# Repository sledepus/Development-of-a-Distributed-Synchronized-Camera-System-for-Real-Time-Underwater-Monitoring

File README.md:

# Development of a Distributed Synchronized Camera System for Real-Time Underwater Monitoring
<div style="text-align: center;">
    
</div>

This is the Git repository of the bachelor thesis "Development of a Distributed Synchronized Camera System for Real-Time Underwater Monitoring", carried out at the University of Agder by students from the Mechatronics and Electronics engineering programs.

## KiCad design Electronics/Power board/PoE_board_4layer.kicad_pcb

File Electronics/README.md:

# KiCAD projects for power board and sensor board
BOM for boards are found in their respective folder. PCBs were ordered from JLCPCB, with the power board requiring a specific stackup which can be found in "Specifications for JLCPCB.txt". The sensor board could be ordered with the normal stackup.

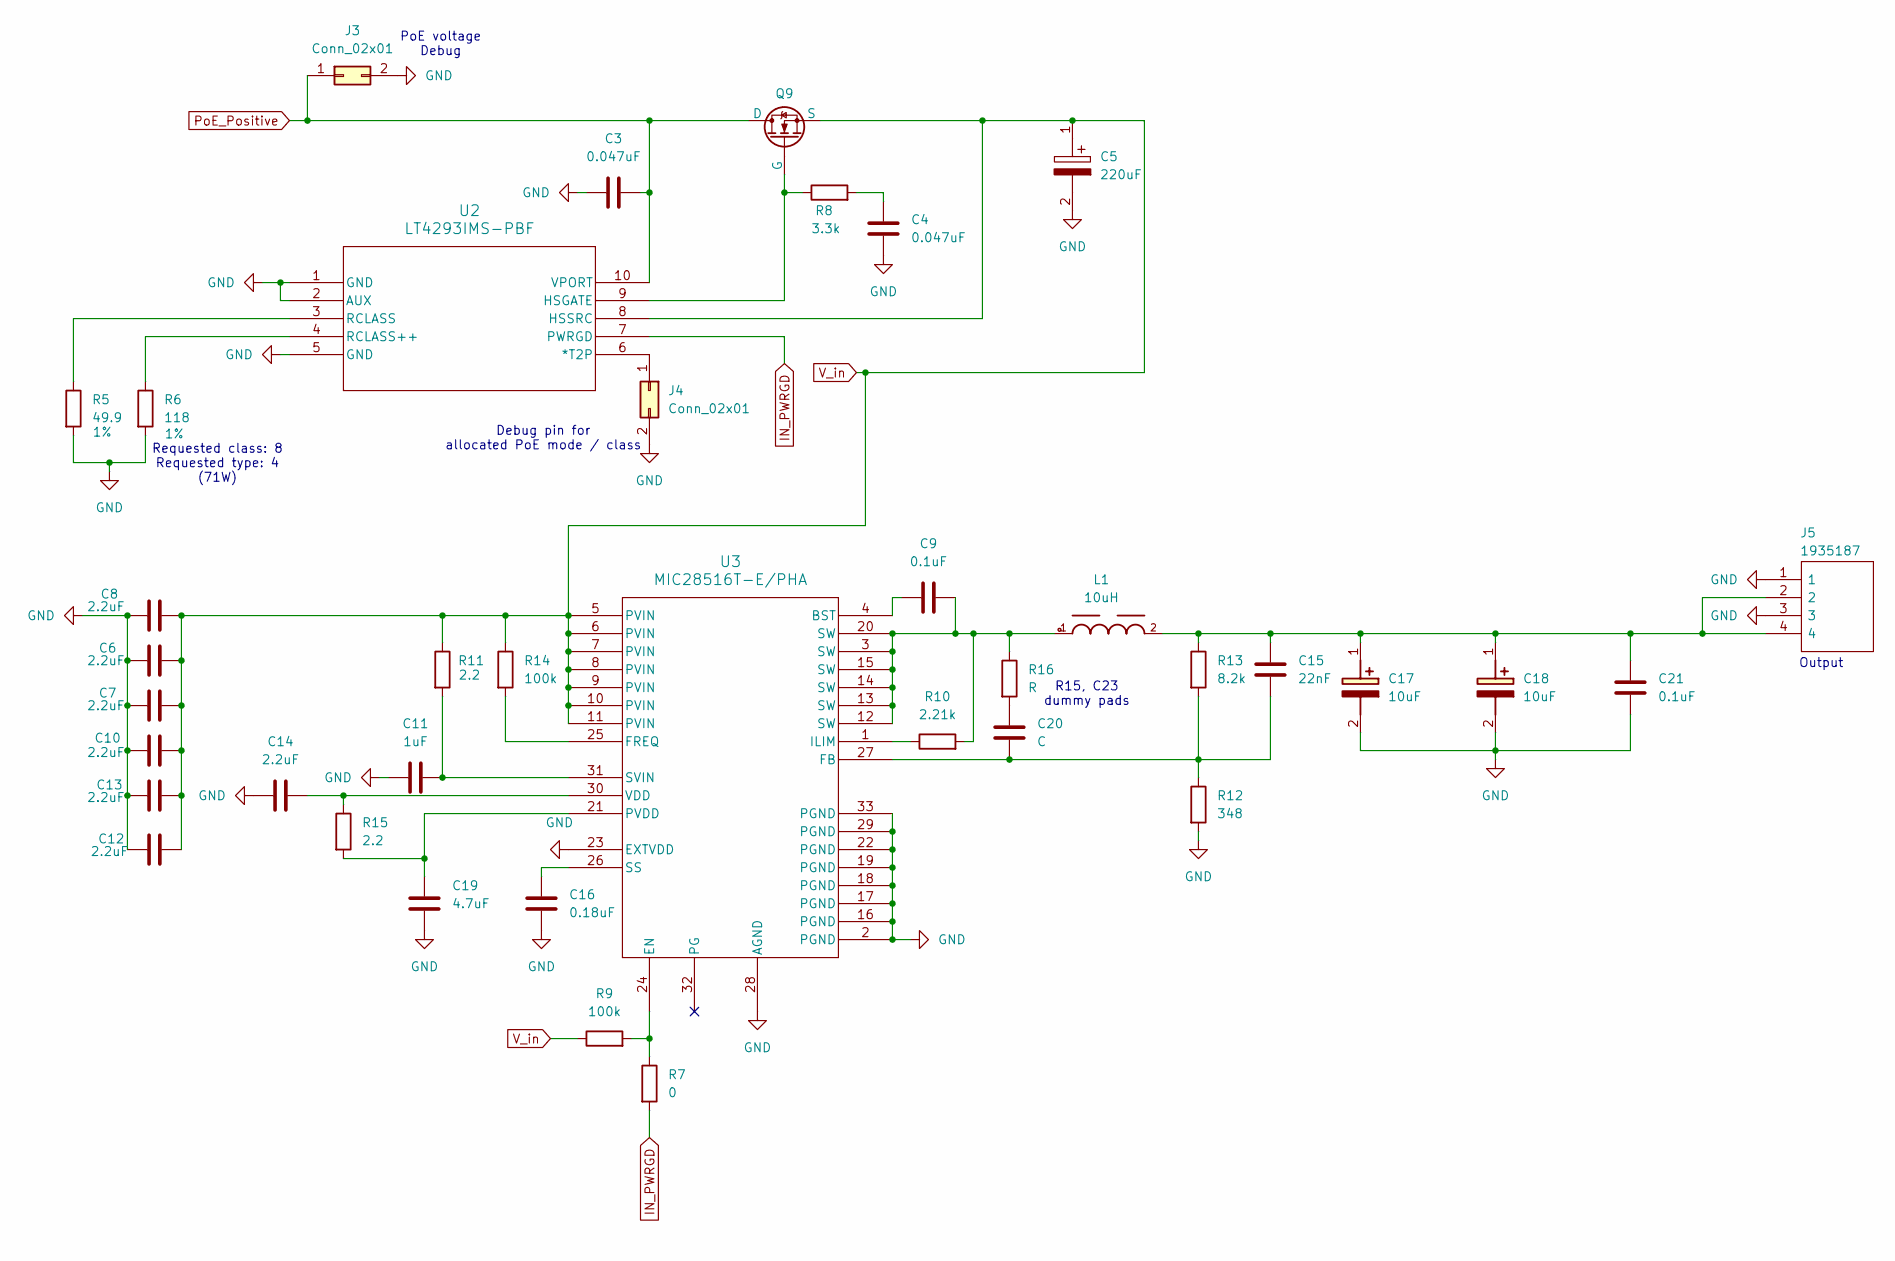
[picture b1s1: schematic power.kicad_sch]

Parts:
C3, C4: 0.047uF; C_1206_3216Metric_Pad1.33x1.80mm_HandSolder
C5: 220uF; CAPPRD500W65D1250H2700; Mouser Part Number 667-EEU-FS2A221B
C6, C7, C8, C10, C12, C13, C14: 2.2uF; C_1206_3216Metric
C9: 0.1uF; C_0603_1608Metric_Pad1.08x0.95mm_HandSolder
C11: 1uF; C_0603_1608Metric_Pad1.08x0.95mm_HandSolder
C15: 22nF; C_0603_1608Metric_Pad1.08x0.95mm_HandSolder
C16: 0.18uF; C_0603_1608Metric_Pad1.08x0.95mm_HandSolder
C17, C18: 10uF; 16SVF82M; Mouser Part Number 667-20SVPA10M
C19: 4.7uF; C_1206_3216Metric_Pad1.33x1.80mm_HandSolder
C20: C; C_1206_3216Metric_Pad1.33x1.80mm_HandSolder
C21: 0.1uF; C_1206_3216Metric_Pad1.33x1.80mm_HandSolder
J3, J4: Conn_02x01; PinHeader_2x01_P2.54mm_Vertical
J5: 1935187; Mouser Part Number 651-1935187
L1: 10uH; WE-XHMI_1090
Q9: PSMN040-100MSE; LFPAK33
R5: 49.9; R_0603_1608Metric_Pad0.98x0.95mm_HandSolder; Tolerance 1%
R6: 118; R_0603_1608Metric_Pad0.98x0.95mm_HandSolder; Tolerance 1%
R7: 0; R_1206_3216Metric_Pad1.30x1.75mm_HandSolder
R8: 3.3k; R_0603_1608Metric_Pad0.98x0.95mm_HandSolder
R9, R14: 100k; R_0603_1608Metric_Pad0.98x0.95mm_HandSolder
R10: 2.21k; R_0603_1608Metric_Pad0.98x0.95mm_HandSolder
R11, R15: 2.2; R_0603_1608Metric_Pad0.98x0.95mm_HandSolder
R12: 348; R_0603_1608Metric_Pad0.98x0.95mm_HandSolder
R13: 8.2k; R_0603_1608Metric_Pad0.98x0.95mm_HandSolder
R16: R; R_1206_3216Metric_Pad1.30x1.75mm_HandSolder
U2: LT4293IMS-PBF; 05-08-1661_ADI
U3: MIC28516T-E/PHA; VQFN32_6X6_3EP_PHA_MCH

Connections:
GND: C3.1, C4.2, C5.2, C6.1, C7.1, C8.1, C10.1, C11.2, C12.1, C13.1, C14.1, C16.2, C17.2 (-), C18.2 (-), C19.2, C21.2, J3.2, J4.2, J5.1, J5.3, R5.2, R6.2, R12.2, U2.1 (GND), U2.2 (AUX), U2.5 (GND), U3.2 (PGND), U3.16 (PGND), U3.17 (PGND), U3.18 (PGND), U3.19 (PGND), U3.22 (PGND), U3.23 (EXTVDD), U3.28 (AGND), U3.29 (PGND), U3.33 (PGND); also elsewhere on the board
IN_PWRGD: R7.2, U2.7 (PWRGD); also elsewhere on the board
unnamed: C4.1, R8.2
unnamed: C9.2, L1.1, R10.2, R16.1, U3.3 (SW), U3.12 (SW), U3.13 (SW), U3.14 (SW), U3.15 (SW), U3.20 (SW)
unnamed: C15.1, C17.1 (+), C18.1 (+), C21.1, J5.2, J5.4, L1.2, R13.1
unnamed: C20.1, R16.2
unnamed: J4.1, U2.6 (*T2P)
unnamed: Q9.4 (G), R8.1, U2.9 (HSGATE)
unnamed: R5.1, U2.3 (RCLASS)
unnamed: R6.1, U2.4 (RCLASS++)
unnamed: C9.1, U3.4 (BST)
unnamed: R7.1, R9.2, U3.24 (EN)
unnamed: C15.2, C20.2, R12.1, R13.2, U3.27 (FB)
unnamed: R14.2, U3.25 (FREQ)
unnamed: R10.1, U3.1 (ILIM)
unnamed: C19.1, R15.2, U3.21 (PVDD)
unnamed: C16.1, U3.26 (SS)
unnamed: C11.1, R11.2, U3.31 (SVIN)
unnamed: C14.2, R15.1, U3.30 (VDD)
PoE_Positive: C3.2, J3.1, Q9.5 (D), U2.10 (VPORT); also elsewhere on the board
V_in: C5.1, C6.2, C7.2, C8.2, C10.2, C12.2, C13.2, Q9.1 (S), Q9.2 (S), Q9.3 (S), R9.1, R11.1, R14.1, U2.8 (HSSRC), U3.5 (PVIN), U3.6 (PVIN), U3.7 (PVIN), U3.8 (PVIN), U3.9 (PVIN), U3.10 (PVIN), U3.11 (PVIN)

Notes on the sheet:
Requested class: 8 Requested type: 4 (71W)
PoE voltage Debug
Output
Debug pin for allocated PoE mode / class
R15, C23 dummy pads

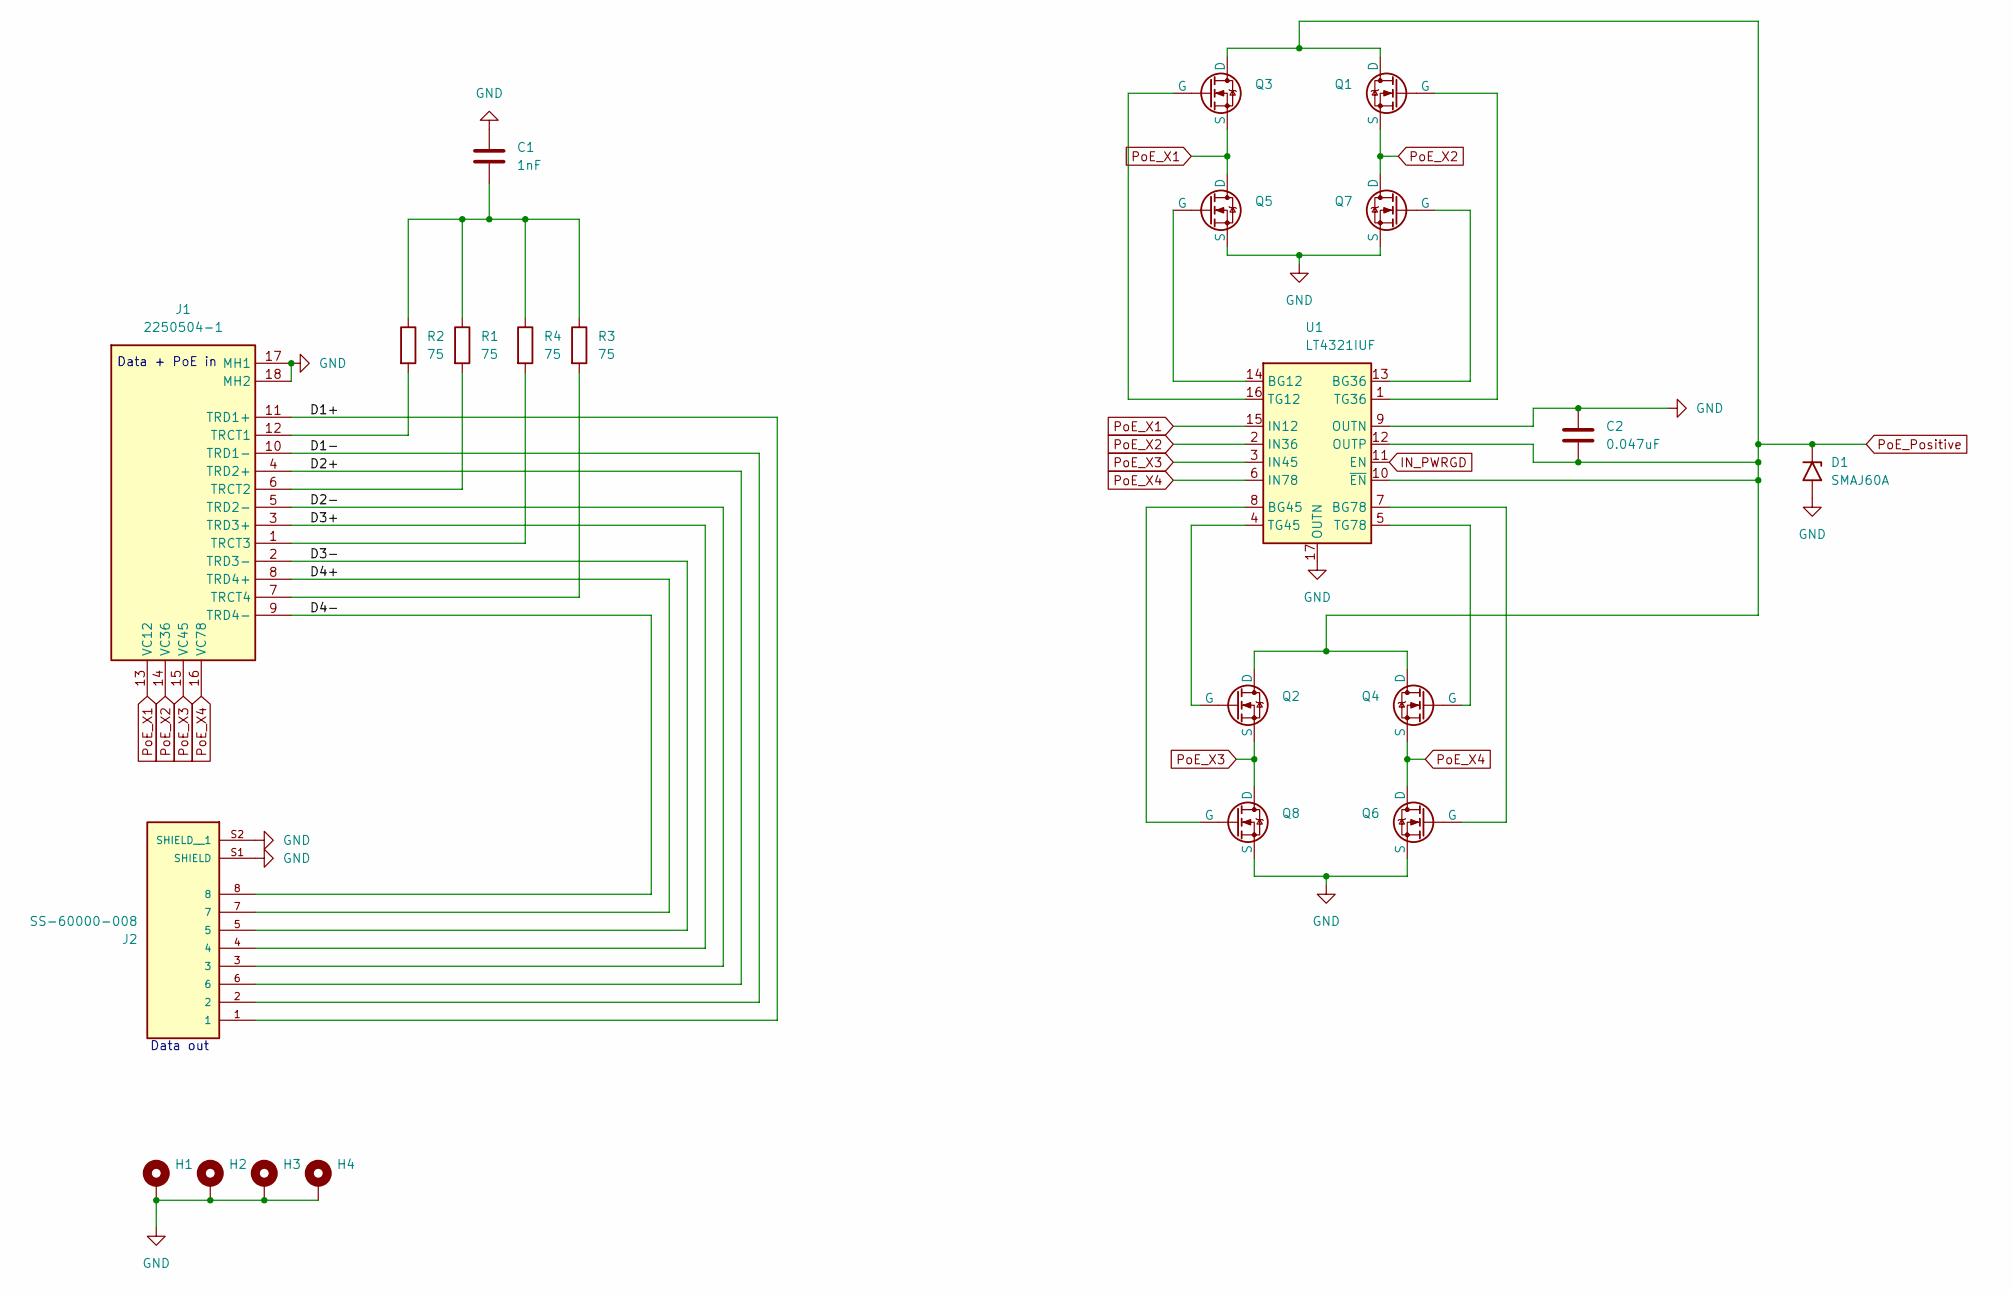
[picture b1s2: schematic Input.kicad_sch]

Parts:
C1: 1nF; C_1808_4520Metric_Pad1.72x2.30mm_HandSolder
C2: 0.047uF; C_1206_3216Metric_Pad1.33x1.80mm_HandSolder
D1: SMAJ60A; D_SMA
H1, H2, H3, H4: MountingHole_Pad; MountingHole_3.2mm_M3_Pad
J1: 2250504-1; 22505041; Mouser Part Number 530-2250504-1
J2: SS-60000-008; BEL_SS-60000-008; PARTREV C6
Q1, Q2, Q3, Q4, Q5, Q6, Q7, Q8: PSMN040-100MSE; LFPAK33
R1, R2, R3, R4: 75; R_1206_3216Metric_Pad1.30x1.75mm_HandSolder
U1: LT4321IUF; QFN-16-1EP_4x4mm_P0.65mm_EP2.15x2.15mm

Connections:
/Input/D1+: J1.11 (TRD1+), J2.1
/Input/D1-: J1.10 (TRD1-), J2.2
/Input/D2+: J1.4 (TRD2+), J2.6
/Input/D2-: J1.5 (TRD2-), J2.3
/Input/D3+: J1.3 (TRD3+), J2.4
/Input/D3-: J1.2 (TRD3-), J2.5
/Input/D4+: J1.8 (TRD4+), J2.7
/Input/D4-: J1.9 (TRD4-), J2.8
GND: C1.1, C2.1, D1.2 (A2), H1.1, H2.1, H3.1, H4.1, J1.17 (MH1), J1.18 (MH2), J2.S1 (SHIELD), J2.S2 (SHIELD__1), Q5.1 (S), Q5.2 (S), Q5.3 (S), Q6.1 (S), Q6.2 (S), Q6.3 (S), Q7.1 (S), Q7.2 (S), Q7.3 (S), Q8.1 (S), Q8.2 (S), Q8.3 (S), U1.9 (OUTN), U1.17 (OUTN); also elsewhere on the board
IN_PWRGD: U1.11 (EN); also elsewhere on the board
unnamed: C1.2, R1.1, R2.1, R3.1, R4.1
unnamed: J1.12 (TRCT1), R2.2
unnamed: J1.6 (TRCT2), R1.2
unnamed: J1.1 (TRCT3), R4.2
unnamed: J1.7 (TRCT4), R3.2
unnamed: Q1.4 (G), U1.1 (TG36)
unnamed: Q2.4 (G), U1.4 (TG45)
unnamed: Q3.4 (G), U1.16 (TG12)
unnamed: Q4.4 (G), U1.5 (TG78)
unnamed: Q5.4 (G), U1.14 (BG12)
unnamed: Q6.4 (G), U1.7 (BG78)
unnamed: Q7.4 (G), U1.13 (BG36)
unnamed: Q8.4 (G), U1.8 (BG45)
PoE_Positive: C2.2, D1.1 (A1), Q1.5 (D), Q2.5 (D), Q3.5 (D), Q4.5 (D), U1.10 (~EN), U1.12 (OUTP); also elsewhere on the board
PoE_X1: J1.13 (VC12), Q3.1 (S), Q3.2 (S), Q3.3 (S), Q5.5 (D), U1.15 (IN12)
PoE_X2: J1.14 (VC36), Q1.1 (S), Q1.2 (S), Q1.3 (S), Q7.5 (D), U1.2 (IN36)
PoE_X3: J1.15 (VC45), Q2.1 (S), Q2.2 (S), Q2.3 (S), Q8.5 (D), U1.3 (IN45)
PoE_X4: J1.16 (VC78), Q4.1 (S), Q4.2 (S), Q4.3 (S), Q6.5 (D), U1.6 (IN78)

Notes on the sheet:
Data + PoE in
Data out

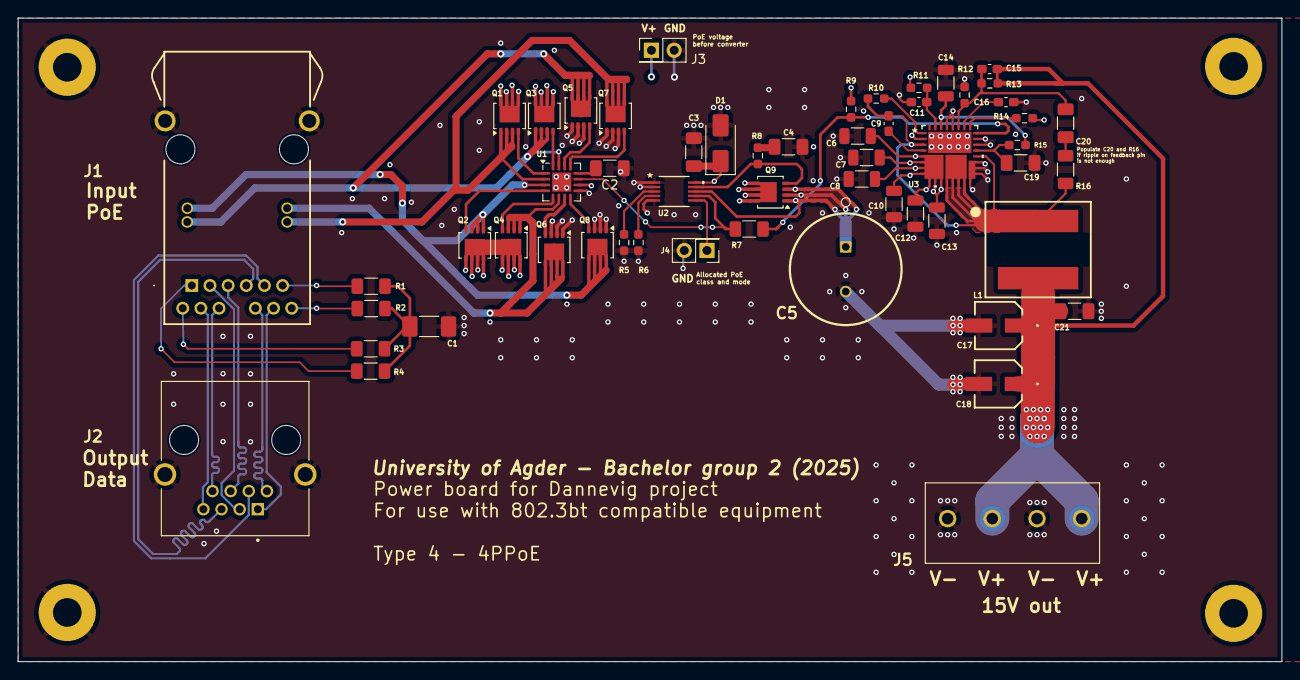
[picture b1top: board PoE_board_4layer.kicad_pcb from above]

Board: 4 copper layers, 141.4 x 72.0 mm, 60 parts (0 on the bottom side), 46 nets.

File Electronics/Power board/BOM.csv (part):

Reference,Value,,Footprint,Qty,DNP,,Cost,Link,,,,,,,,,,,,Total cost:,616.35
C1,1nF,,Capacitor_SMD:C_1808_4520Metric_Pad1.72x2.30mm_HandSolder,1,,,6.33,https://no.mouser.com/ProductDetail/TDK/C4520X7R3D102K130KA?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,,,,,,,,,,,,,
C2,0.047uF,,Capacitor_SMD:C_1206_3216Metric_Pad1.33x1.80mm_HandSolder,1,,,5.06,https://no.mouser.com/ProductDetail/TDK/C3216X7R2A474K160AA?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,,,,,,,,,,,,,
C3,0.047uF,,Capacitor_SMD:C_1206_3216Metric_Pad1.33x1.80mm_HandSolder,1,,,5.06,https://no.mouser.com/ProductDetail/TDK/C3216X7R2A474K160AA?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,,,,,,,,,,,,,
C4,0.047uF,,Capacitor_SMD:C_1206_3216Metric_Pad1.33x1.80mm_HandSolder,1,,,5.06,https://no.mouser.com/ProductDetail/TDK/C3216X7R2A474K160AA?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,,,,,,,,,,,,,
C5,220uF,,local symbols:CAPPRD500W65D1250H2700,1,,,18.63,https://no.mouser.com/ProductDetail/Panasonic/EEU-FS2A221B?q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,,,,,,,,,,,,,
C6,2.2uF,,Capacitor_SMD:C_1206_3216Metric,1,,,5.06,https://no.mouser.com/ProductDetail/Samsung-Electro-Mechanic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,,,,,,,,,,,,,
C7,2.2uF,,Capacitor_SMD:C_1206_3216Metric,1,,,5.06,https://no.mouser.com/ProductDetail/Samsung-Electro-Mechanic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,,,,,,,,,,,,,
C8,2.2uF,,Capacitor_SMD:C_1206_3216Metric,1,,,5.06,https://no.mouser.com/ProductDetail/Samsung-Electro-Mechanic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,,,,,,,,,,,,,
C9,0.1uF,,Capacitor_SMD:C_0603_1608Metric_Pad1.08x0.95mm_HandSolder,1,,,1.15,https://no.mouser.com/ProductDetail/Samsung-Electro-Mechanic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,,,,,,,,,,,,,
C10,2.2uF,,Capacitor_SMD:C_1206_3216Metric,1,,,5.06,https://no.mouser.com/ProductDetail/Samsung-Electro-Mechanic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,,,,,,,,,,,,,
C11,1uF,,Capacitor_SMD:C_0603_1608Metric_Pad1.08x0.95mm_HandSolder,1,,,3.11,https://no.mouser.com/ProductDetail/TDK/C1608X7R2A105K080AC?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,,,,,,,,,,,,,
C12,2.2uF,,Capacitor_SMD:C_1206_3216Metric,1,,,5.06,https://no.mouser.com/ProductDetail/Samsung-Electro-Mechanic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,,,,,,,,,,,,,
C13,2.2uF,,Capacitor_SMD:C_1206_3216Metric,1,,,5.06,https://no.mouser.com/ProductDetail/Samsung-Electro-Mechanic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,,,,,,,,,,,,,
C14,2.2uF,,Capacitor_SMD:C_1206_3216Metric,1,,,5.06,https://no.mouser.com/ProductDetail/Samsung-Electro-Mechanic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,,,,,,,,,,,,,
C15,22nF,,Capacitor_SMD:C_0603_1608Metric_Pad1.08x0.95mm_HandSolder,1,,,1.15,https://no.mouser.com/ProductDetail/TDK/C1608X7R1H223K080AA?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,,,,,,,,,,,,,
C16,0.18uF,,Capacitor_SMD:C_0603_1608Metric_Pad1.08x0.95mm_HandSolder,1,,,2.07,https://no.mouser.com/ProductDetail/Murata-Electronics/GRM18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,,,,,,,,,,,,,
C17,20SVPA10M,,local symbols:16SVF82M,1,,,10.12,https://no.mouser.com/ProductDetail/Panasonic/20SVPA10M?qs=k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,,,,,,,,,,,,,
C18,20SVPA10M,,local symbols:16SVF82M,1,,,10.12,https://no.mouser.com/ProductDetail/Panasonic/20SVPA10M?qs=k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,,,,,,,,,,,,,
C19,4.7uF,,Capacitor_SMD:C_1206_3216Metric_Pad1.33x1.80mm_HandSolder,1,,,3.34,https://no.mouser.com/ProductDetail/TDK/C3216X7R1E475K160AC?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,,,,,,,,,,,,,
C20,C,,Capacitor_SMD:C_0603_1608Metric_Pad1.08x0.95mm_HandSolder,1,,,DNP,DNP,,,,,,,,,,,,,
C21,0.1uF,,Capacitor_SMD:C_1206_3216Metric_Pad1.33x1.80mm_HandSolder,1,,,2.76,https://no.mouser.com/ProductDetail/TDK/C3216X7R2A104M160AA?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,,,,,,,,,,,,,
D1,SMAJ60A,,Diode_SMD:D_SMA,1,,,3.11,https://no.mouser.com/ProductDetail/Littelfuse/SMAJ60A?qs=JJ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,,,,,,,,,,,,,
J1,2250504-1,,local symbols:22505041,1,,,103.33,https://no.mouser.com/ProductDetail/TRP-Connector-Bel/225050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,,,,,,,,,,,,,
J2,SS-60000-008,,local symbols:BEL_SS-60000-008,1,,,42.71,https://no.mouser.com/ProductDetail/Stewart-Connector-Bel/SS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,,,,,,,,,,,,,
J3,Conn_02x01,,Connector_PinHeader_2.54mm:PinHeader_2x01_P2.54mm_Vertical,1,,,DNP,DNP,,,,,,,,,,,,,
J4,Conn_02x01,,Connector_PinHeader_2.54mm:PinHeader_2x01_P2.54mm_Vertical,1,,,DNP,DNP,,,,,,,,,,,,,
J5,1935187,,local symbols:1935187,1,,,11.16,https://no.mouser.com/ProductDetail/Phoenix-Contact/1935187?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,,,,,,,,,,,,,
L1,10uH,,local symbols:WE-XHMI_1090,1,,,63.77,https://no.mouser.com/ProductDetail/Wurth-Elektronik/7443936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,,,,,,,,,,,,,
Q1,PSMN040-100MSE,,Package_TO_SOT_SMD:LFPAK33,1,,,12.95,https://no.mouser.com/ProductDetail/Nexperia/PSMN040-100MSEX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,,,,,,,,,,,,,
Q2,PSMN040-100MSE,,Package_TO_SOT_SMD:LFPAK33,1,,,12.95,https://no.mouser.com/ProductDetail/Nexperia/PSMN040-100MSEX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,,,,,,,,,,,,,
Q3,PSMN040-100MSE,,Package_TO_SOT_SMD:LFPAK33,1,,,12.95,https://no.mouser.com/ProductDetail/Nexperia/PSMN040-100MSEX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,,,,,,,,,,,,,
Q4,PSMN040-100MSE,,Package_TO_SOT_SMD:LFPAK33,1,,,12.95,https://no.mouser.com/ProductDetail/Nexperia/PSMN040-100MSEX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,,,,,,,,,,,,,
Q5,PSMN040-100MSE,,Package_TO_SOT_SMD:LFPAK33,1,,,12.95,https://no.mouser.com/ProductDetail/Nexperia/PSMN040-100MSEX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,,,,,,,,,,,,,
Q6,PSMN040-100MSE,,Package_TO_SOT_SMD:LFPAK33,1,,,12.95,https://no.mouser.com/ProductDetail/Nexperia/PSMN040-100MSEX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,,,,,,,,,,,,,
Q7,PSMN040-100MSE,,Package_TO_SOT_SMD:LFPAK33,1,,,12.95,https://no.mouser.com/ProductDetail/Nexperia/PSMN040-100MSEX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,,,,,,,,,,,,,
Q8,PSMN040-100MSE,,Package_TO_SOT_SMD:LFPAK33,1,,,12.95,https://no.mouser.com/ProductDetail/Nexperia/PSMN040-100MSEX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,,,,,,,,,,,,,
Q9,PSMN040-100MSE,,Package_TO_SOT_SMD:LFPAK33,1,,,12.95,https://no.mouser.com/ProductDetail/Nexperia/PSMN040-100MSEX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,,,,,,,,,,,,,
R1,75,,Resistor_SMD:R_1206_3216Metric_Pad1.30x1.75mm_HandSolder,1,,,1.15,https://no.mouser.com/ProductDetail/YAGEO/RT1206DRE0775RL?qs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,,,,,,,,,,,,,
R2,75,,Resistor_SMD:R_1206_3216Metric_Pad1.30x1.75mm_HandSolder,1,,,1.15,https://no.mouser.com/ProductDetail/YAGEO/RT1206DRE0775RL?qs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,,,,,,,,,,,,,
R3,75,,Resistor_SMD:R_1206_3216Metric_Pad1.30x1.75mm_HandSolder,1,,,1.15,https://no.mouser.com/ProductDetail/YAGEO/RT1206DRE0775RL?qs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,,,,,,,,,,,,,
R4,75,,Resistor_SMD:R_1206_3216Metric_Pad1.30x1.75mm_HandSolder,1,,,1.15,https://no.mouser.com/ProductDetail/YAGEO/RT1206DRE0775RL?qs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,,,,,,,,,,,,,
R5,49.9,,Resistor_SMD:R_0603_1608Metric_Pad0.98x0.95mm_HandSolder,1,,,1.5,https://no.mouser.com/ProductDetail/Vishay-Dale/RCS060349R9F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,,,,,,,,,,,,,
R6,118,,Resistor_SMD:R_0603_1608Metric_Pad0.98x0.95mm_HandSolder,1,,,1.22,https://no.mouser.com/ProductDetail/KOA-Speer/RK73H1JTTD1180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,,,,,,,,,,,,,
R7,0,,Resistor_SMD:R_1206_3216Metric_Pad1.30x1.75mm_HandSolder,1,,,1.15,https://no.mouser.com/ProductDetail/Vishay-Dale/CRCW12060000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,,,,,,,,,,,,,
R8,3.3k,,Resistor_SMD:R_0603_1608Metric_Pad0.98x0.95mm_HandSolder,1,,,1.15,https://no.mouser.com/ProductDetail/YAGEO/AC0603JR-073K3L?qs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,,,,,,,,,,,,,
R9,100k,,Resistor_SMD:R_0603_1608Metric_Pad0.98x0.95mm_HandSolder,1,,,1.15,https://no.mouser.com/ProductDetail/YAGEO/AT0603FRE07100KL?q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,,,,,,,,,,,,,
R10,2.21k,,Resistor_SMD:R_0603_1608Metric_Pad0.98x0.95mm_HandSolder,1,,,1.15,https://no.mouser.com/ProductDetail/Panasonic/ERJ-3EKF2211V?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,,,,,,,,,,,,,
R11,2.2,,Resistor_SMD:R_0603_1608Metric_Pad0.98x0.95mm_HandSolder,1,,,2.42,https://no.mouser.com/ProductDetail/Vishay-Dale/RCS06032R20F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,,,,,,,,,,,,,
R12,348,,Resistor_SMD:R_0603_1608Metric_Pad0.98x0.95mm_HandSolder,1,,,2.42,https://no.mouser.com/ProductDetail/Panasonic/ERJ-H3EF3480V?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,,,,,,,,,,,,,
R13,8.2k,,Resistor_SMD:R_0603_1608Metric_Pad0.98x0.95mm_HandSolder,1,,,1.61,https://no.mouser.com/ProductDetail/Vishay-Dale/RCS06038K20F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,,,,,,,,,,,,,
R14,100k,,Resistor_SMD:R_0603_1608Metric_Pad0.98x0.95mm_HandSolder,1,,,1.15,https://no.mouser.com/ProductDetail/YAGEO/AT0603FRE07100KL?q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,,,,,,,,,,,,,
R15,2.2,,Resistor_SMD:R_0603_1608Metric_Pad0.98x0.95mm_HandSolder,1,,,2.42,https://no.mouser.com/ProductDetail/Vishay-Dale/RCS06032R20F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,,,,,,,,,,,,,
R16,R,,Resistor_SMD:R_0603_1608Metric_Pad0.98x0.95mm_HandSolder,1,,,DNP,DNP,,,,,,,,,,,,,
U1,LT4321IUF,,Package_DFN_QFN:QFN-16-1EP_4x4mm_P0.65mm_EP2.15x2.15mm,1,,,46.39,https://www.digikey.no/no/products/detail/analog-devices-inc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,,,,,,,,,,,,,
U2,LT4293IMS-PBF,,footprints:05-08-1661_ADI,1,,,58.08,https://no.mouser.com/ProductDetail/Analog-Devices/LT4293IMS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,,,,,,,,,,,,,
U3,MIC28516T-E/PHA,,footprints:VQFN32_6X6_3EP_PHA_MCH,1,,,39.93,https://no.mouser.com/ProductDetail/Microchip-Technology/MIC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,,,,,,,,,,,,,
,,,,,,,,,,,,,,,,,,,,,
,,,,,,,,,,,,,,,,,,,,,
,,,,,,,,,,,,,,,,,,,,,
,,,,,,,,,,,,,,,,,,,,,
,Komponenter til 1 kort,616.35,,,,,,,,,,,,,,,,,,,
,Bestilling av 5 kort (uten stencil),832.44,,,,,,,,,,,,,,,,,,,
,eller,,,,,,,,,,,,,,,,,,,,
,Bestilling av 5 kort (med stencil),1172.45,,,,,,,,,,,,,,,,,,,
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
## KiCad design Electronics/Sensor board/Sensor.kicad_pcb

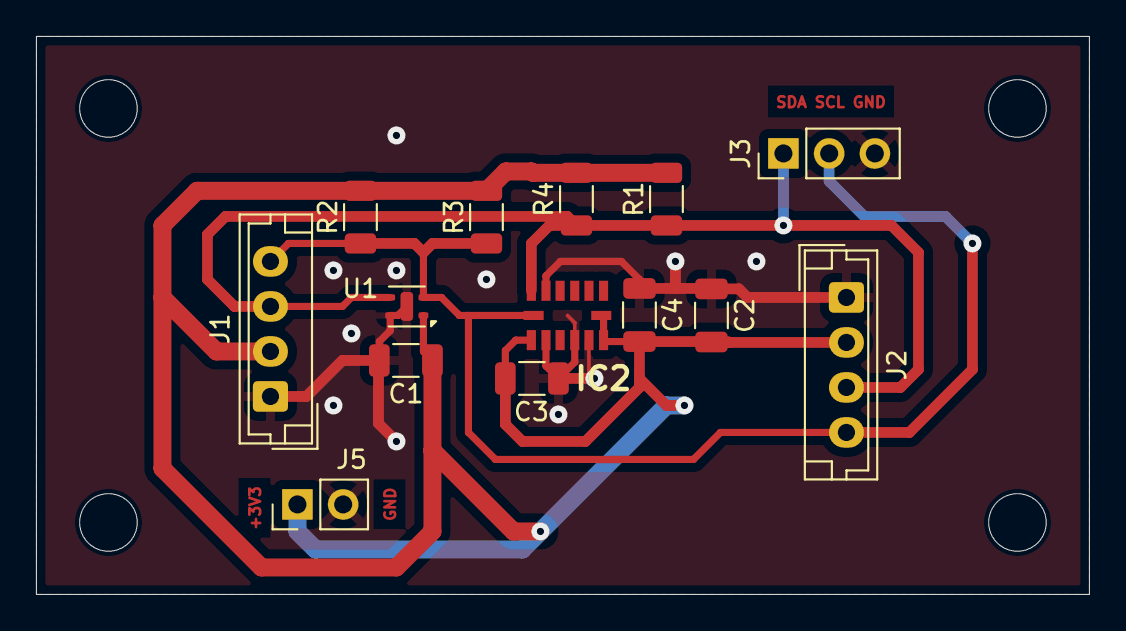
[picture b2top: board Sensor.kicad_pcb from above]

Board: 2 copper layers, 58.5 x 31.0 mm, 14 parts (0 on the bottom side), 4 nets.

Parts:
C1: 100nF; C_1206_3216Metric
C2: 1uF; C_1206_3216Metric
C3: 0.1uF; C_1206_3216Metric
C4: 10uF; C_1206_3216Metric
IC2: ADXL345BCCZ; LGA14R80P3X6_300X500X100
J1, J2: Conn_01x04_Socket; JST_EH_B4B-EH-A_1x04_P2.50mm_Vertical
J3: Conn_01x03_Pin; PinHeader_1x03_P2.54mm_Vertical
J5: Conn_01x02_Pin; PinHeader_1x02_P2.54mm_Vertical
R1, R2, R3, R4: 10k; R_1206_3216Metric
U1: SHTC3; Sensirion_DFN-4-1EP_2x2mm_P1mm_EP0.7x1.6mm

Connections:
+3V3: C1.1, C2.2, C3.2, C4.2, IC2.1 (VDD_I/O), IC2.6 (VS), IC2.7 (~CS), J1.2, J2.2, J5.1, R1.2, R2.2, R3.2, R4.2, U1.1 (VDD)
GND: C1.2, C2.1, C3.1, C4.1, IC2.2 (GND_2), IC2.4 (GND_3), IC2.5 (GND), IC2.12 (SDO/ALT_ADDRESS), J1.1, J2.1, J3.3, J5.2, U1.4 (VSS), U1.5 (CP)
unnamed: IC2.14 (SCL/SCLK), J1.4, J2.4, J3.2, R2.1, R3.1, U1.2 (SCL)
unnamed: IC2.13 (SDA/SDI/SDIO), J1.3, J2.3, J3.1, R1.1, R4.1, U1.3 (SDA)

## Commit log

2025-05-22 Created repository
